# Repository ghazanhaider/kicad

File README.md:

# KiCad

## KiCad bindings

Connect:
```
from kipy import KiCad
kicad = KiCad()
board = KiCad.get_board()
print(f"Connected to KiCad {kicad.get_version()}")
print(f"Active Layer is {board.get_active_layer()}")
```

PCB Tracks:
```
board = KiCad().get_board()
for t in board.get_tracks():
    if (t.layer == board.get_active_layer()) & (t.width not in [156400,156500,142500,300000,500000,180000]):
        print("Width: " + str(t.width) + "  Layer: " + str(t.layer) + " Net: " + str(t.net))
        board.add_to_selection(t)
```

### Older PCBNEW bindings:

```
import pcbnew
board = pcbnew.GetBoard()
tracks = board.GetTracks()
layer = board.GetLayerID("Mid.Cu")
fp_list = brd.GetFootprints()
tracks=board.GetTracks()

badtracks=[]
for t in board.GetTracks()
    print("Width: " + str(t.GetWidth()) + "Layer: " + str(t.GetLayer()))
```

https://www.atomic14.com/2022/10/24/kicad-python-scripting-cheat-sheet
https://kicad.mmccoo.com/index.php/2017/02/01/modifying-pcbnew-layout-from-python/

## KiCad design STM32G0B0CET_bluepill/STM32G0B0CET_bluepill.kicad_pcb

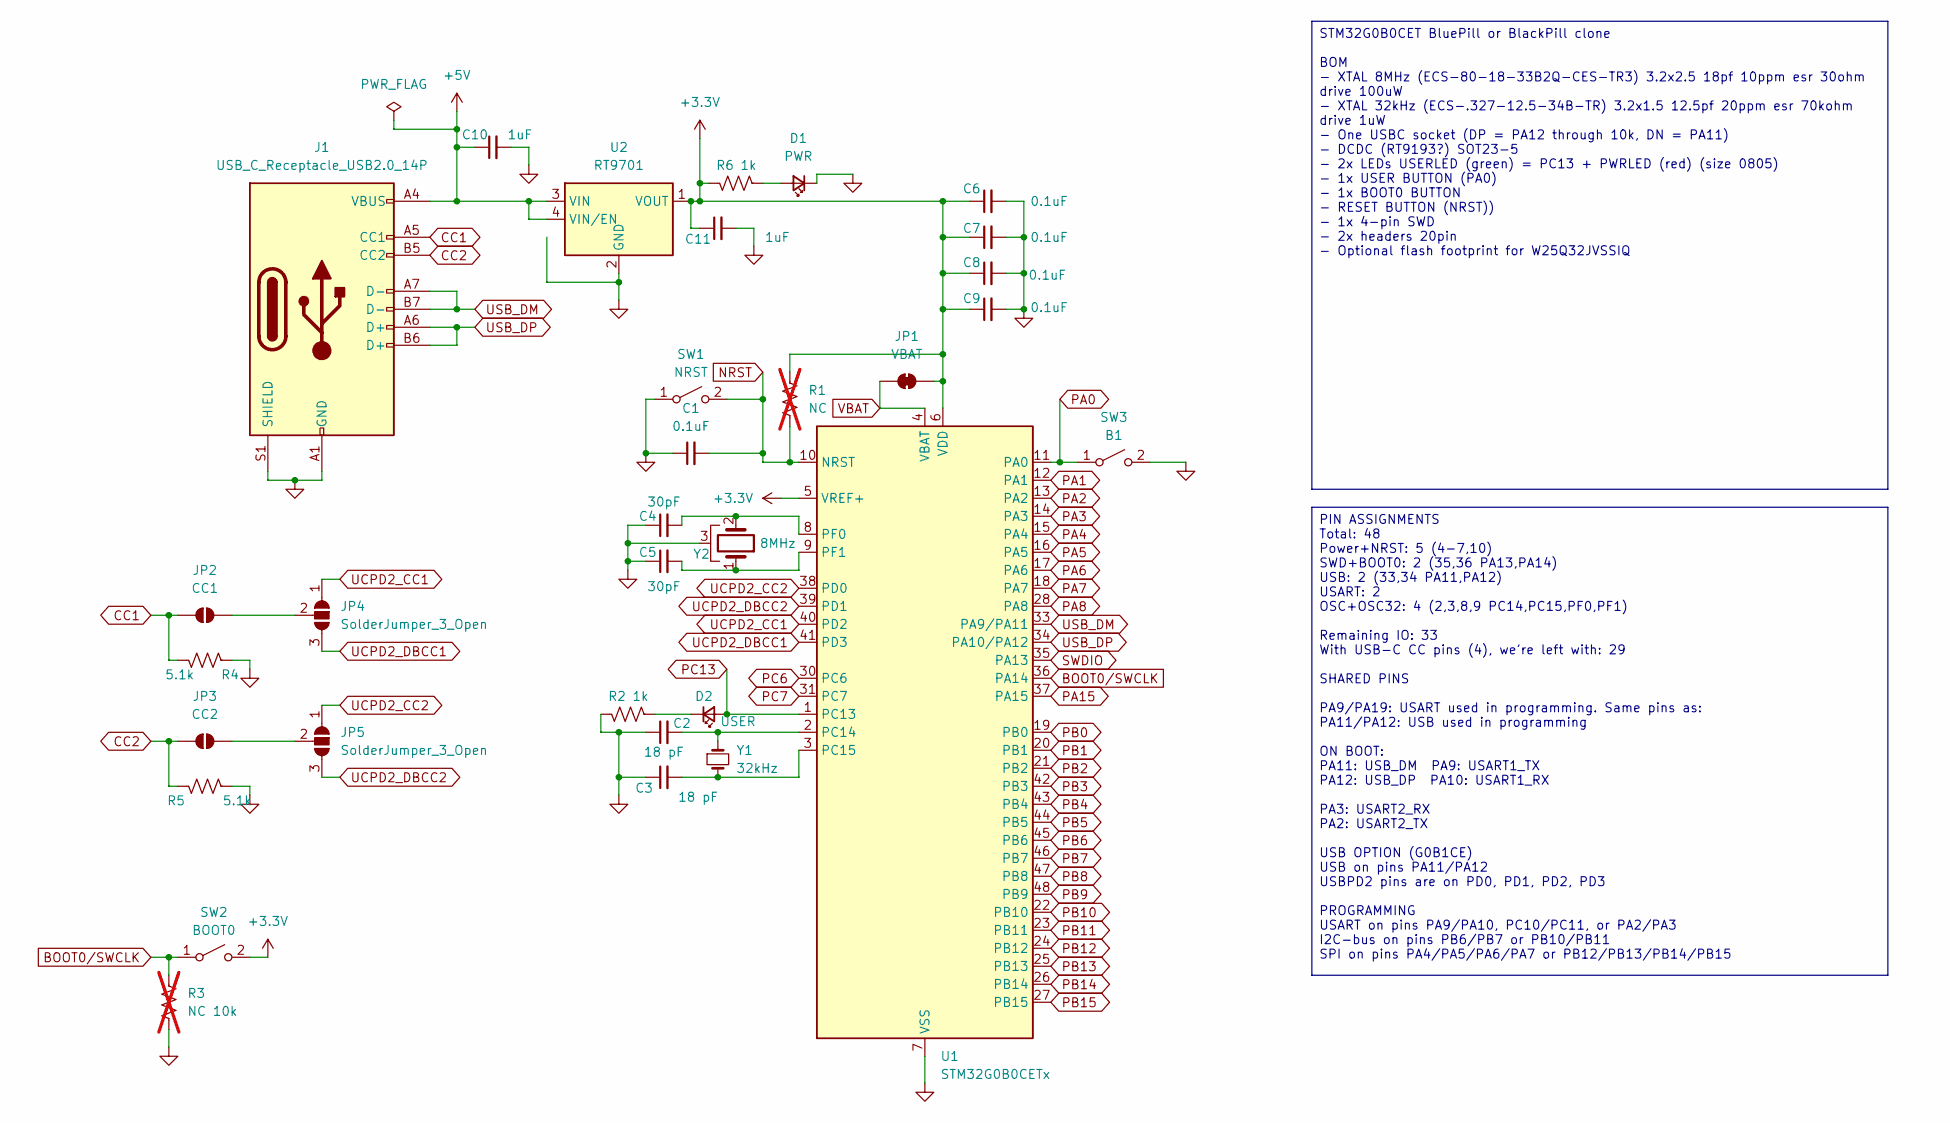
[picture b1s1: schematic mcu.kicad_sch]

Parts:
C1, C6, C7, C8, C9: 0.1uF; C_0603_1608Metric
C2, C3: 18 pF; C_0603_1608Metric
C4, C5: 30pF; C_0603_1608Metric
C10, C11: 1uF; C_0603_1608Metric
D1: PWR; LED_0805_2012Metric
D2: USER; LED_0805_2012Metric
J1: USB_C_Receptacle_USB2.0_14P; USB_C_Receptacle_GCT_USB4105-xx-A_16P_TopMnt_Horizontal
JP1: VBAT; SolderJumper-2_P1.3mm_Bridged_RoundedPad1.0x1.5mm
JP2: CC1; SolderJumper-2_P1.3mm_Open_RoundedPad1.0x1.5mm
JP3: CC2; SolderJumper-2_P1.3mm_Open_RoundedPad1.0x1.5mm
JP4, JP5: SolderJumper_3_Open; SolderJumper-3_P1.3mm_Open_RoundedPad1.0x1.5mm_NumberLabels
R1: NC; R_0603_1608Metric; not fitted
R2, R6: 1k; R_0603_1608Metric
R3: NC 10k; R_0603_1608Metric; not fitted
R4, R5: 5.1k; R_0603_1608Metric
SW1: NRST; SW_SPST_PTS810
SW2: BOOT0; SW_SPST_PTS810
SW3: B1; SW_SPST_PTS810
U1: STM32G0B0CETx; LQFP-48_7x7mm_P0.5mm
U2: RT9701; SOT-23-5
Y1: 32kHz; Crystal_SMD_2012-2Pin_2.0x1.2mm
Y2: 8MHz; Crystal_SMD_3225-4Pin_3.2x2.5mm

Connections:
+3.3V: C6.1, C7.1, C8.1, C9.1, C11.1, JP1.2 (B), R1.1, R6.2, SW2.2 (B), U1.5 (VREF+), U1.6 (VDD), U2.1 (VOUT), U2.5 (VOUT); also elsewhere on the board
+5V: C10.1, J1.A4 (VBUS), J1.A9 (VBUS), J1.B4 (VBUS), J1.B9 (VBUS), U2.3 (VIN), U2.4 (VIN/EN); also elsewhere on the board
BOOT0/SWCLK: R3.1, SW2.1 (A), U1.36 (PA14); also elsewhere on the board
CC1: J1.A5 (CC1), JP2.1 (A), R4.1
CC2: J1.B5 (CC2), JP3.1 (A), R5.2
GND: C1.1, C2.1, C3.1, C4.1, C5.1, C6.2, C7.2, C8.2, C9.2, C10.2, C11.2, D1.1 (K), J1.A1 (GND), J1.A12 (GND), J1.B1 (GND), J1.B12 (GND), J1.S1 (SHIELD), R2.2, R3.2, R4.2, R5.1, SW1.1 (A), SW3.2 (B), U1.7 (VSS), U2.2 (GND), Y2.3; also elsewhere on the board
NRST: C1.2, R1.2, SW1.2 (B), U1.10 (NRST); also elsewhere on the board
unnamed: D1.2 (A), R6.1
unnamed: D2.1 (K), R2.1
unnamed: JP2.2 (B), JP4.2 (C)
unnamed: JP3.2 (B), JP5.2 (C)
unnamed: C2.2, U1.2 (PC14), Y1.1
unnamed: C3.2, U1.3 (PC15), Y1.2
unnamed: C4.2, U1.8 (PF0), Y2.2
unnamed: C5.2, U1.9 (PF1), Y2.1
PA0: SW3.1 (A), U1.11 (PA0); also elsewhere on the board
PA1: U1.12 (PA1); also elsewhere on the board
PA2: U1.13 (PA2); also elsewhere on the board
PA3: U1.14 (PA3); also elsewhere on the board
PA4: U1.15 (PA4); also elsewhere on the board
PA5: U1.16 (PA5); also elsewhere on the board
PA6: U1.17 (PA6); also elsewhere on the board
PA7: U1.18 (PA7); also elsewhere on the board
PA8: U1.28 (PA8); also elsewhere on the board
PA15: U1.37 (PA15); also elsewhere on the board
PB0: U1.19 (PB0); also elsewhere on the board
PB1: U1.20 (PB1); also elsewhere on the board
PB2: U1.21 (PB2); also elsewhere on the board
PB3: U1.42 (PB3); also elsewhere on the board
PB4: U1.43 (PB4); also elsewhere on the board
PB5: U1.44 (PB5); also elsewhere on the board
PB6: U1.45 (PB6); also elsewhere on the board
PB7: U1.46 (PB7); also elsewhere on the board
PB8: U1.47 (PB8); also elsewhere on the board
PB9: U1.48 (PB9); also elsewhere on the board
PB10: U1.22 (PB10); also elsewhere on the board
PB11: U1.23 (PB11); also elsewhere on the board
PB12: U1.24 (PB12); also elsewhere on the board
PB13: U1.25 (PB13); also elsewhere on the board
PB14: U1.26 (PB14); also elsewhere on the board
PB15: U1.27 (PB15); also elsewhere on the board
PC6: U1.30 (PC6); also elsewhere on the board
PC7: U1.31 (PC7); also elsewhere on the board
PC13: D2.2 (A), U1.1 (PC13); also elsewhere on the board
SWDIO: U1.35 (PA13); also elsewhere on the board
UCPD2_CC1: JP4.1 (A), U1.40 (PD2); also elsewhere on the board
UCPD2_CC2: JP5.1 (A), U1.38 (PD0); also elsewhere on the board
UCPD2_DBCC1: JP4.3 (B), U1.41 (PD3)
UCPD2_DBCC2: JP5.3 (B), U1.39 (PD1); also elsewhere on the board
USB_DM: J1.A7 (D-), J1.B7 (D-), U1.33 (PA9/PA11)
USB_DP: J1.A6 (D+), J1.B6 (D+), U1.34 (PA10/PA12)
VBAT: JP1.1 (A), U1.4 (VBAT); also elsewhere on the board

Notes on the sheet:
STM32G0B0CET BluePill or BlackPill clone BOM - XTAL 8MHz (ECS-80-18-33B2Q-CES-TR3) 3.2x2.5 18pf 10ppm esr 30ohm drive 100uW - XTAL 32kHz (ECS-.327-12.5-34B-TR) 3.2x1.5 12.5pf 20ppm esr 70kohm drive 1uW - One USBC socket (DP = PA12 through 10k, DN = PA11) - DCDC (RT9193?) SOT23-5 - 2x LEDs USERLED (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
PIN ASSIGNMENTS Total: 48 Power+NRST: 5 (4-7,10) SWD+BOOT0: 2 (35,36 PA13,PA14) USB: 2 (33,34 PA11,PA12) USART: 2 OSC+OSC32: 4 (2,3,8,9 PC14,PC15,PF0,PF1) Remaining IO: 33 With USB-C CC pins (4), we're left with: 29 SHARED PINS PA9/PA19: USART used in programming. Same pins as: PA11/PA12: USB used 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

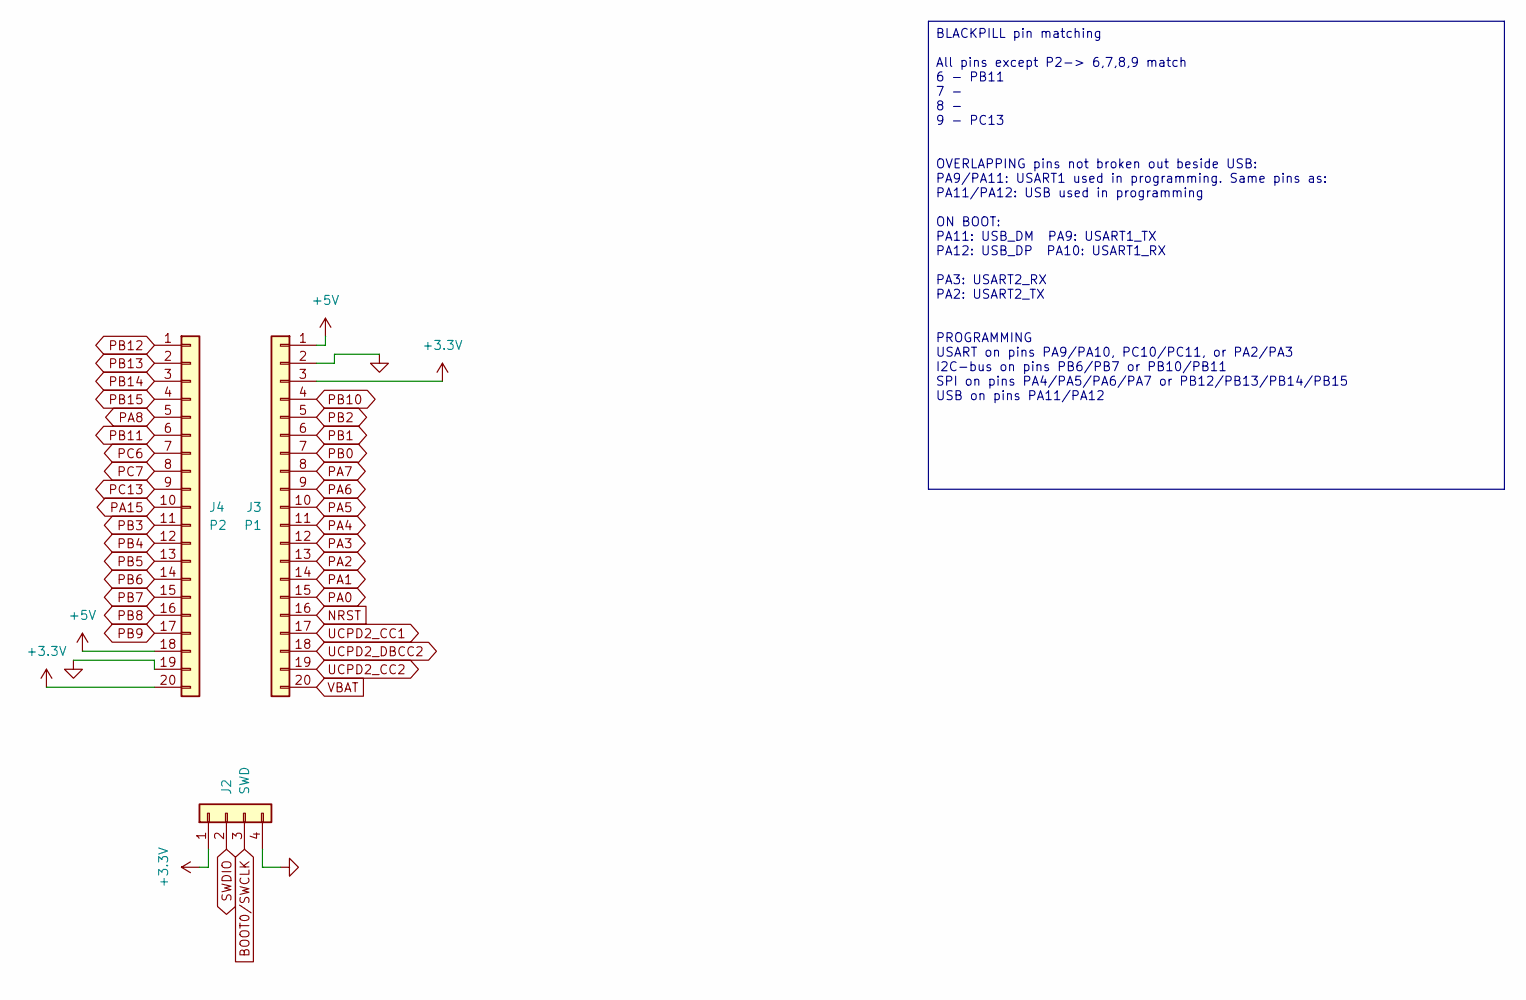
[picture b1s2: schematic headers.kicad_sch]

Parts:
J2: SWD; PinHeader_1x04_P2.54mm_Vertical
J3: P1; PinHeader_1x20_P2.54mm_Vertical
J4: P2; PinHeader_1x20_P2.54mm_Vertical

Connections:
+3.3V: J2.1, J3.3, J4.20; also elsewhere on the board
+5V: J3.1, J4.18; also elsewhere on the board
BOOT0/SWCLK: J2.3; also elsewhere on the board
GND: J2.4, J3.2, J4.19; also elsewhere on the board
NRST: J3.16; also elsewhere on the board
PA0: J3.15; also elsewhere on the board
PA1: J3.14; also elsewhere on the board
PA2: J3.13; also elsewhere on the board
PA3: J3.12; also elsewhere on the board
PA4: J3.11; also elsewhere on the board
PA5: J3.10; also elsewhere on the board
PA6: J3.9; also elsewhere on the board
PA7: J3.8; also elsewhere on the board
PA8: J4.5; also elsewhere on the board
PA15: J4.10; also elsewhere on the board
PB0: J3.7; also elsewhere on the board
PB1: J3.6; also elsewhere on the board
PB2: J3.5; also elsewhere on the board
PB3: J4.11; also elsewhere on the board
PB4: J4.12; also elsewhere on the board
PB5: J4.13; also elsewhere on the board
PB6: J4.14; also elsewhere on the board
PB7: J4.15; also elsewhere on the board
PB8: J4.16; also elsewhere on the board
PB9: J4.17; also elsewhere on the board
PB10: J3.4; also elsewhere on the board
PB11: J4.6; also elsewhere on the board
PB12: J4.1; also elsewhere on the board
PB13: J4.2; also elsewhere on the board
PB14: J4.3; also elsewhere on the board
PB15: J4.4; also elsewhere on the board
PC6: J4.7; also elsewhere on the board
PC7: J4.8; also elsewhere on the board
PC13: J4.9; also elsewhere on the board
SWDIO: J2.2; also elsewhere on the board
UCPD2_CC1: J3.17; also elsewhere on the board
UCPD2_CC2: J3.19; also elsewhere on the board
UCPD2_DBCC2: J3.18; also elsewhere on the board
VBAT: J3.20; also elsewhere on the board

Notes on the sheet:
BLACKPILL pin matching All pins except P2-> 6,7,8,9 match 6 - PB11 7 - 8 - 9 - PC13 OVERLAPPING pins not broken out beside USB: PA9/PA11: USART1 used in programming. Same pins as: PA11/PA12: USB used in programming ON BOOT: PA11: USB_DM PA9: USART1_TX PA12: USB_DP PA10: USART1_RX PA3: USART2_RX PA2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

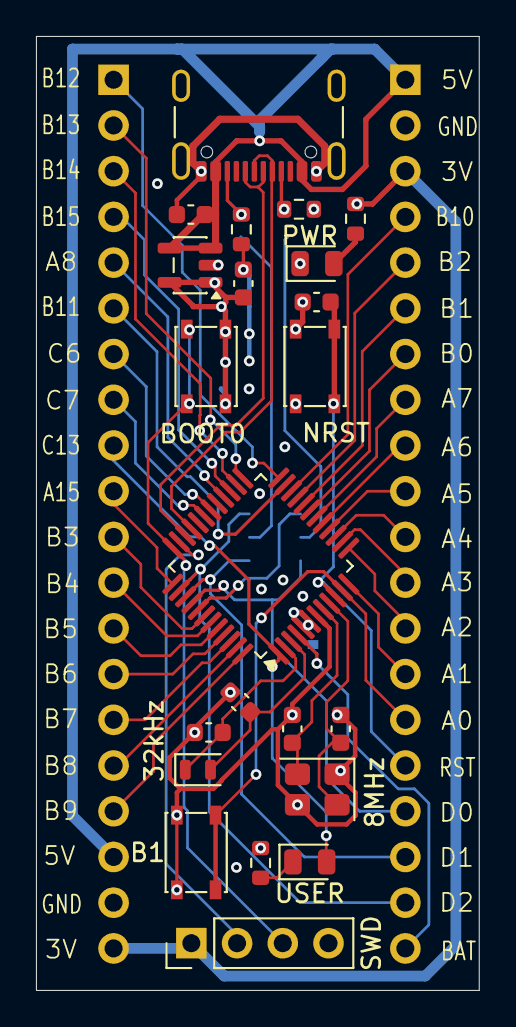
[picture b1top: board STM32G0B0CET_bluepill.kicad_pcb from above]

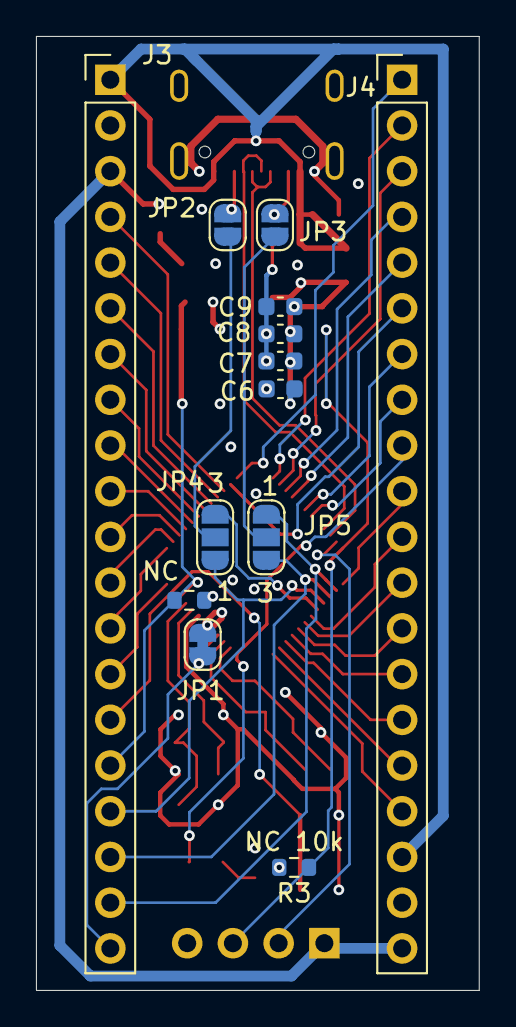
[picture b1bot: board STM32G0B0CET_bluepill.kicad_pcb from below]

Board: 4 copper layers, 24.6 x 53.0 mm, 35 parts (13 on the bottom side), 52 nets.

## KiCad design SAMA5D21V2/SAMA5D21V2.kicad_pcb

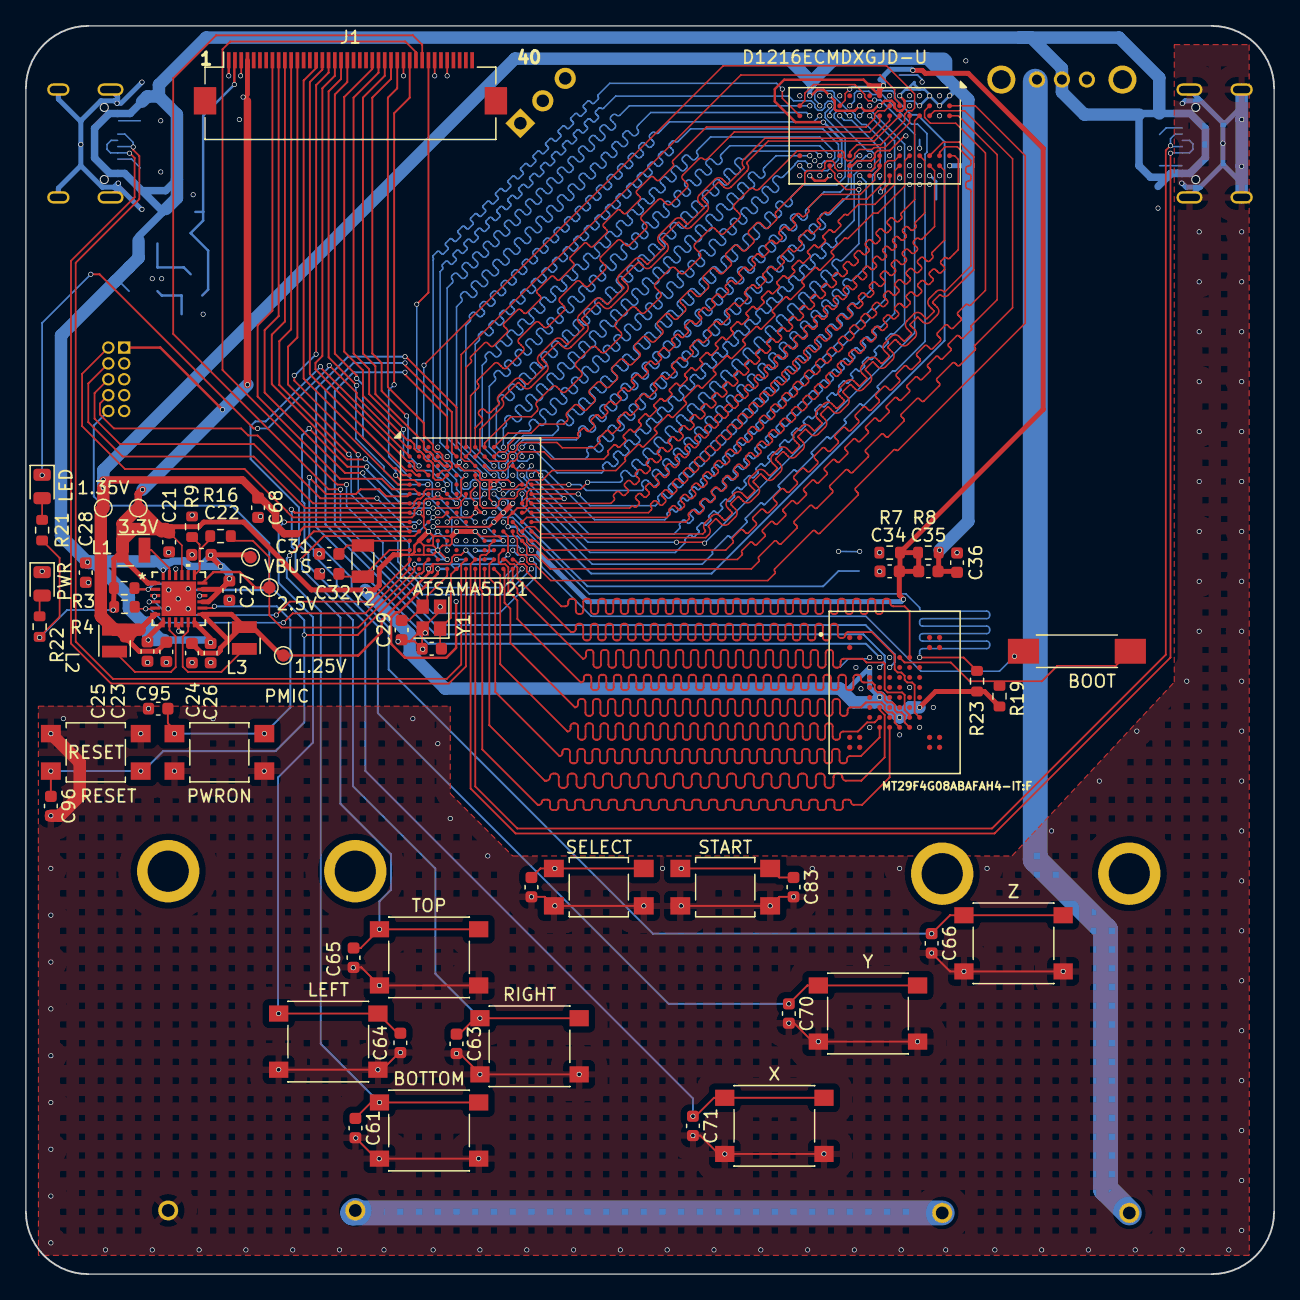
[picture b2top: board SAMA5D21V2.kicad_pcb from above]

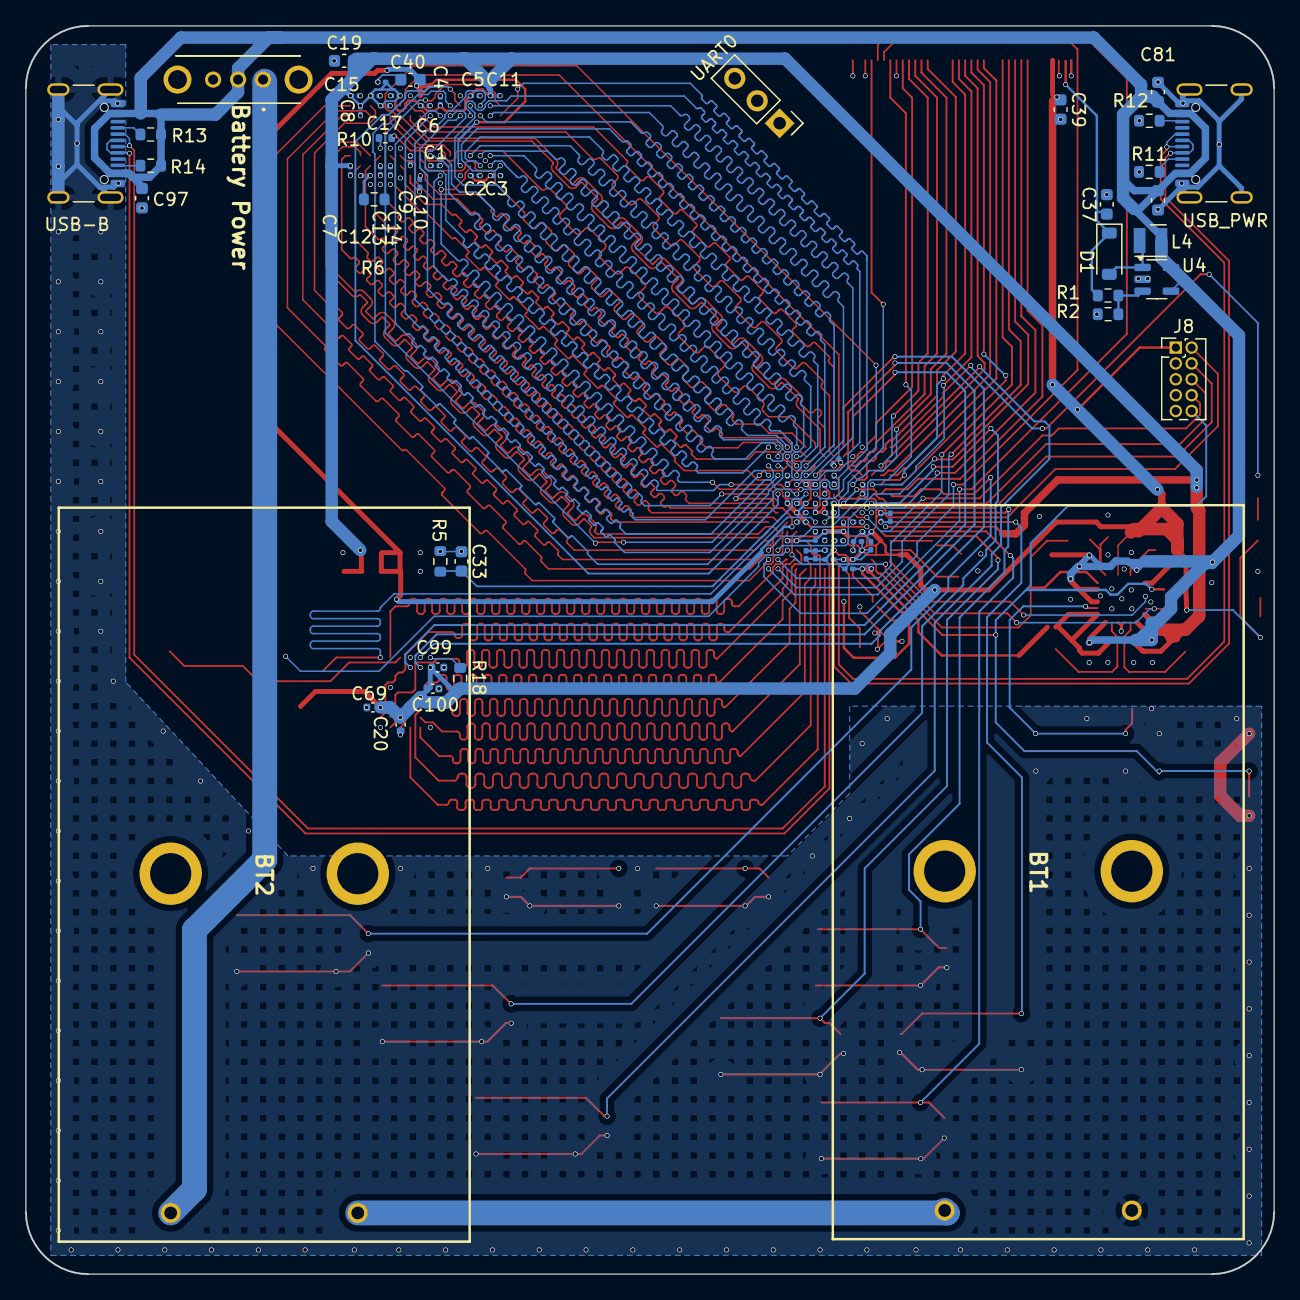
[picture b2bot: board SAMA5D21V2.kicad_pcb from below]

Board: 6 copper layers, 100.0 x 100.0 mm, 149 parts (83 on the bottom side), 136 nets.

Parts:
BT1, BT2: 2.4V; 2462
C1, C2, C3, C4, C5, C6, C7, C8, C9, C10, C11, C12, C13, C14, C15, C16, C17, C18, C38, C41, C42, C43, C44, C45, C46, C47, C48, C49, C50, C51, C52, C53, C54, C55, C57, C58, C67, C72, C74, C76, C78, C79: 100nF; C_0201_0603Metric
C19, C37, C68: 1uF; C_0603_1608Metric
C20, C69, C99, C100: 100nF; C_0402_1005Metric
C21, C23, C24: 22uF; C_0603_1608Metric
C22, C25, C26, C27, C28, C36, C39, C80, C81, C97: 4.7uF; C_0603_1608Metric
C29, C30, C31, C32: 16pF; C_0603_1608Metric
C33: 22pF; C_0603_1608Metric
C34, C35, C40, C61, C63, C64, C65, C66, C70, C71, C82, C83, C95, C96: 100nF; C_0603_1608Metric
C56, C59, C62, C73, C75, C77, C84: 1uF; C_0201_0603Metric
C60: 10nF; C_0201_0603Metric
D1: 1N5819HW-7-F; D_SOD-123
D2: LED; LED_0805_2012Metric
D3: PWR; LED_0805_2012Metric
IC1: D1216ECMDXGJD-U; Micron_FBGA-96_7.5x13.5mm_Layout9x16_P0.8mm
J1: Conn_01x40; Hirose_FH12-40S-0.5SH_1x40-1MP_P0.50mm_Horizontal
J8: SWD; PinHeader_2x05_P1.27mm_Vertical
J10: UART0; PinHeader_1x03_P2.54mm_Vertical
JP1: BOOT; SW_SPST_REED_CT05-XXXX-G1
L1, L2, L3: 2.2uH; L_Wurth_WE-LQSH-2512
L4: 10uH; L_Wurth_WE-LQSH-2512
P1: USB_PWR; USB_C_Receptacle_GCT_USB4105-xx-A_16P_TopMnt_Horizontal
P2: USB-B; USB_C_Receptacle_GCT_USB4105-xx-A_16P_TopMnt_Horizontal
R1: 92.82k; R_0603_1608Metric
R2: 5.1k; R_0603_1608Metric
R3, R4, R6: 100k; R_0603_1608Metric
R5: 23.2k 1%; R_0603_1608Metric
R7, R8: 6.8k 1%; R_0603_1608Metric
R9: 182k; R_0603_1608Metric
R10: 240R 1%; R_0402_1005Metric
R11, R12: 5.1k 1%; R_0603_1608Metric
R13, R14: 56k 1%; R_0603_1608Metric
R15: 5.62k 1%; R_0201_0603Metric
R16: 324k; R_0603_1608Metric
R18, R19: 470k; R_0603_1608Metric
R21, R22, R23: 1k; R_0603_1608Metric
SW1: BOTTOM; SW_Push_1P1T_NO_6x6mm_H9.5mm
SW2: PWRON; SW_SPST_TL3305A
SW3: RESET; SW_SPST_TL3305A
SW4: RIGHT; SW_Push_1P1T_NO_6x6mm_H9.5mm
SW5: LEFT; SW_Push_1P1T_NO_6x6mm_H9.5mm
SW6: TOP; SW_Push_1P1T_NO_6x6mm_H9.5mm
SW7: Z; SW_Push_1P1T_NO_6x6mm_H9.5mm
SW8: Y; SW_Push_1P1T_NO_6x6mm_H9.5mm
SW9: X; SW_Push_1P1T_NO_6x6mm_H9.5mm
SW10: Battery Power; EG1213
SW11: SELECT; SW_SPST_TL3305A
SW12: START; SW_SPST_TL3305A
TP1: VBUS; TestPoint_Pad_D1.0mm
TP2: 3.3V; TestPoint_Pad_D1.0mm
TP3: 1.35V; TestPoint_Pad_D1.0mm
TP4: 1.25V; TestPoint_Pad_D1.0mm
TP5: 2.5V; TestPoint_Pad_D1.0mm
U1: ATSAMA5D21; Microchip_TFBGA-196_11x11mm_Layout14x14_P0.75mm_SMD
U2: PMIC; VQFN24_RMB_MCH
U3: MT29F4G08ABAFAH4-IT:F; BGA63C80P10X12_1050X1300X100N
U4: AP3012; SOT-23-5
Y1: 12MHz; Crystal_SMD_2520-4Pin_2.5x2.0mm
Y2: 32.768kHz; Crystal_SMD_3215-2Pin_3.2x1.5mm

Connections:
+1V25: C24.2, C38.2, C48.1, C49.1, C50.1, C51.1, C52.1, C62.2, C72.1, C73.1, C84.1, L3.1, TP4.1, U1.E8 (VDDCORE), U1.G8 (VDDCORE), U1.H8 (VDDCORE), U1.H9 (VDDCORE), U1.J5 (VDDCORE), U1.M7 (VDDUTMIC), U1.P3 (VDDPLLA), U2.13 (OUT3)
+1V35: C1.2, C2.2, C3.2, C4.2, C5.2, C6.2, C7.2, C8.2, C9.2, C10.2, C11.2, C12.2, C13.2, C14.2, C15.2, C16.2, C17.2, C18.2, C19.2, C23.1, C35.2, C36.1, C41.1, C42.1, C43.1, C44.1, C45.1, C46.1, C47.1, C60.1, C68.1, IC1.A1 (VDDQ_1), IC1.A8 (VDDQ_2), IC1.B2 (VDD_1), IC1.C1 (VDDQ_3), IC1.C9 (VDDQ_4), IC1.D2 (VDDQ_5), IC1.D9 (VDD_2), IC1.E9 (VDDQ_6), IC1.F1 (VDDQ_7), IC1.G7 (VDD_3), IC1.H2 (VDDQ_8), IC1.H9 (VDDQ_9), IC1.K2 (VDD_4), IC1.K8 (VDD_5), IC1.N1 (VDD_6), IC1.N9 (VDD_7), IC1.R1 (VDD_8), IC1.R9 (VDD_9), L2.1, R6.2, R8.1, TP3.1, U1.C6 (VDDIODDR), U1.E10 (VDDIODDR), U1.E12 (VDDIODDR), U1.G10 (VDDIODDR), U1.G12 (VDDIODDR), U1.H11 (VDDIODDR), U1.J10 (VDDIODDR), U2.6 (OUT2)
+3V3: C20.2, C21.1, C39.1, C54.1, C55.1, C56.1, C57.1, C58.1, C59.1, C67.2, C69.2, C74.1, C75.1, C76.1, C77.1, C78.1, C79.1, C99.2, C100.2, J1.4, J8.1 (VTref), L1.2, R3.2, R4.2, R18.1, R19.2, R21.1, R22.1, R23.2, TP2.1, U1.D7 (VDDIOP0), U1.F4 (VDDIOP0), U1.H2 (VDDANA), U1.K3 (VDDANA), U1.K6 (VDDAUDIOPLL), U1.K7 (VDDUTMII), U1.K8 (VDDIOP1), U1.L2 (ADVREF), U1.L11 (VDDIOP1), U1.M4 (VDDBU), U1.N5 (VDDOSC), U2.1 (OUT1), U2.21 (LEN), U3.D3 (VCC), U3.G4 (VCC), U3.H8 (VCC), U3.J6 (VCC)
/DDR3/A0: IC1.N3 (A0), U1.E11 (DDR_A0)
/DDR3/A1: IC1.P7 (A1), U1.C11 (DDR_A1)
/DDR3/A2: IC1.P3 (A2), U1.B12 (DDR_A2)
/DDR3/A3: IC1.N2 (A3), U1.A12 (DDR_A3)
/DDR3/A4: IC1.P8 (A4), U1.D11 (DDR_A4)
/DDR3/A5: IC1.P2 (A5), U1.D14 (DDR_A5)
/DDR3/A6: IC1.R8 (A6), U1.B14 (DDR_A6)
/DDR3/A7: IC1.R2 (A7), U1.D9 (DDR_A7)
/DDR3/A8: IC1.T8 (A8), U1.C10 (DDR_A8)
/DDR3/A9: IC1.R3 (A9), U1.D10 (DDR_A9)
/DDR3/A10/AP: IC1.L7 (A10/AP), U1.F9 (DDR_A10)
/DDR3/A11: IC1.R7 (A11), U1.A11 (DDR_A11)
/DDR3/A12/BC#: IC1.N7 (A12/BC#), U1.B11 (DDR_A12)
/DDR3/A13: IC1.T3 (A13), U1.E13 (DDR_A13)
/DDR3/BA0: IC1.M2 (BA0), U1.F13 (DDR_BA0)
/DDR3/BA1: IC1.N8 (BA1), U1.G13 (DDR_BA1)
/DDR3/BA2: IC1.M3 (BA2), U1.F14 (DDR_BA2)
/DDR3/CAS#: IC1.K3 (CAS#), U1.C13 (DDR_CAS)
/DDR3/CK: IC1.J7 (CK), U1.A13 (DDR_CLK)
/DDR3/CK#: IC1.K7 (CK#), U1.B13 (DDR_CLKN)
/DDR3/CKE: IC1.K9 (CKE), U1.E14 (DDR_CKE)
/DDR3/CS#: IC1.L2 (CS#), U1.F11 (DDR_CS)
/DDR3/DDR_VREF: C34.2, C35.1, C40.1, IC1.H1 (VREFDQ), IC1.M8 (VREFCA), R7.1, R8.2, U1.C12 (DDR_VREF), U1.H12 (DDR_VREF)
/DDR3/DML: IC1.E7 (DML), U1.D8 (DDR_DQM0)
/DDR3/DMU: IC1.D3 (DMU), U1.G14 (DDR_DQM1)
/DDR3/DQL0: IC1.E3 (DQL0), U1.A9 (DDR_D4)
/DDR3/DQL1: IC1.F7 (DQL1), U1.B9 (DDR_D3)
/DDR3/DQL2: IC1.F2 (DQL2), U1.C8 (DDR_D2)
/DDR3/DQL3: IC1.F8 (DQL3), U1.C9 (DDR_D5)
/DDR3/DQL4: IC1.H3 (DQL4), U1.B7 (DDR_D0)
/DDR3/DQL5: IC1.H8 (DQL5), U1.B10 (DDR_D7)
/DDR3/DQL6: IC1.G2 (DQL6), U1.A7 (DDR_D1)
/DDR3/DQL7: IC1.H7 (DQL7), U1.A10 (DDR_D6)
/DDR3/DQSLN: IC1.G3 (DQSL#), U1.A8 (DDR_DQSN0)
/DDR3/DQSLP: IC1.F3 (DQSL), U1.B8 (DDR_DQS0)
/DDR3/DQSUN: IC1.B7 (DQSU#), U1.K13 (DDR_DQSN1)
/DDR3/DQSUP: IC1.C7 (DQSU), U1.K14 (DDR_DQS1)
/DDR3/DQU0: IC1.D7 (DQU0), U1.H13 (DDR_D8)
/DDR3/DQU1: IC1.C3 (DQU1), U1.L13 (DDR_D12)
/DDR3/DQU2: IC1.C8 (DQU2), U1.H14 (DDR_D9)
/DDR3/DQU3: IC1.C2 (DQU3), U1.L14 (DDR_D13)
/DDR3/DQU4: IC1.A7 (DQU4), U1.J14 (DDR_D11)
/DDR3/DQU5: IC1.A2 (DQU5), U1.K12 (DDR_D15)
/DDR3/DQU6: IC1.B8 (DQU6), U1.J13 (DDR_D10)
/DDR3/DQU7: IC1.A3 (DQU7), U1.J12 (DDR_D14)
/DDR3/RAS#: IC1.J3 (RAS#), U1.C14 (DDR_RAS)
/DDR3/WE#: IC1.L3 (WE#), U1.A14 (DDR_WE)
/DDR3/~DDR_RESET: IC1.T2 (RESET#), R6.1, U1.D13 (~DDR_RESET)
/NAND/NAND_CE: JP1.2 (B), R19.1, U3.C6 (CE#)
/Power/SHDN: U1.N1 (SHDN), U2.3 (PWRHLD)
/Power/START: C95.1, SW2.2, U2.14 (nSTRT)
/Power/WKUP: R4.1, U1.P1 (WKUP), U2.5 (nSTRTO)
/USB/USBAN: P1.A7 (D-), P1.B7 (D-), U1.P7 (HHSDMA)
/USB/USBAP: P1.A6 (D+), P1.B6 (D+), U1.N7 (HHSDPA)
/USB/USBBN: P2.A7 (D-), P2.B7 (D-), U1.P8 (HHSDMB)
/USB/USBBP: P2.A6 (D+), P2.B6 (D+), U1.N8 (HHSDPB)
/USB/VBG: R15.2, U1.L7 (VBG)
BUTTON1: C61.1, SW1.2, U1.K1 (PD21)
BUTTON2: C63.1, SW4.2, U1.K2 (PD23)
BUTTON3: C64.1, SW5.2, U1.J1 (PD20)
BUTTON4: C65.1, SW6.2, U1.H1 (PD11)
BUTTON5: C66.1, SW7.2, U1.F1 (PB28)
BUTTON6: C70.1, SW8.2, U1.G3 (PD18)
BUTTON7: C71.1, SW9.2, U1.B1 (PB11)
BUTTON8: C82.1, SW11.2, U1.H3 (PD13)
BUTTON9: C83.1, SW12.2, U1.H4 (PD19)
GNDADIOPLL: BT1.2 (-), C1.1, C2.1, C3.1, C4.1, C5.1, C6.1, C7.1, C8.1, C9.1, C10.1, C11.1, C12.1, C13.1, C14.1, C15.1, C16.1, C17.1, C18.1, C19.1, C20.1, C21.2, C22.2, C23.2, C24.1, C25.2, C26.1, C27.2, C28.1, C29.1, C30.1, C31.2, C32.2, C33.2, C34.1, C36.2, C37.2, C38.1, C39.2, C40.2, C41.2, C42.2, C43.2, C44.2, C45.2, C46.2, C47.2, C48.2, C49.2, C50.2, C51.2, C52.2, C53.2, C54.2, C55.2, C56.2, C57.2, C58.2, C59.2, C60.2, C61.2, C62.1, C63.2, C64.2, C65.2, C66.2, C67.1, C68.2, C69.1, C70.2, C71.2, C72.2, C73.2, C74.2, C75.2, C76.2, C77.2, C78.2, C79.2, C80.2, C81.2, C82.2, C83.2, C84.2, C95.2, C96.2, C97.2, C99.1, C100.1, D3.1 (K), IC1.A9 (VSS_1), IC1.B1 (VSSQ_1), IC1.B3 (VSS_2), IC1.B9 (VSSQ_2), IC1.D1 (VSSQ_3), IC1.D8 (VSSQ_4), IC1.E1 (VSS_3), IC1.E2 (VSSQ_5), IC1.E8 (VSSQ_6), IC1.F9 (VSSQ_7), IC1.G1 (VSSQ_8), IC1.G8 (VSS_4), IC1.G9 (VSSQ_9), IC1.J2 (VSS_5), IC1.J8 (VSS_6), IC1.K1 (ODT), IC1.M1 (VSS_7), IC1.M9 (VSS_8), IC1.P1 (VSS_9), IC1.P9 (VSS_10), IC1.T1 (VSS_11), IC1.T9 (VSS_12), J1.1, J1.3, J1.29, J1.34, J1.36, J8.3 (GND), J8.5 (GND), J8.9 (GNDDetect), J10.1, P1.A1 (GND), P1.A12 (GND), P1.B1 (GND), P1.B12 (GND), P1.S1 (SHIELD), P2.A1 (GND), P2.A12 (GND), P2.B1 (GND), P2.B12 (GND), P2.S1 (SHIELD), R2.2, R5.1, R7.2, R9.2, R10.2, R11.1, R12.1, R15.1, SW1.1, SW2.1, SW3.1, SW4.1, SW5.1, SW6.1, SW7.1, SW8.1, SW9.1, SW11.1, SW12.1, U1.C7 (GNDIODDR), U1.D12 (GNDIODDR), U1.E4 (GNDIOP0), U1.E7 (GNDIOP0), U1.E9 (GNDIODDR), U1.F8 (GNDCORE), U1.F12 (GNDIODDR), U1.G7 (GNDCORE), U1.G9 (GNDCORE), U1.G11 (GNDIODDR), U1.H7 (GNDCORE), U1.H10 (GNDIODDR), U1.J2 (GNDANA), U1.J4 (GNDCORE), U1.J6 (GNDAUDIOPLL), U1.J11 (GNDIODDR), U1.K4 (GNDANA), U1.K9 (GNDIOP1), U1.L6 (GNDDPLL), U1.L8 (GNDUTMII), U1.L12 (GNDIOP1), U1.M5 (GNDBU), U1.M8 (GNDUTMIC), U1.N6 (GNDOSC), U1.P4 (GNDPLLA), U2.4 (LPM), U2.9 (PGND2), U2.10 (PGND3), U2.16 (SGND), U2.22 (PGND1), U2.25 (GND), U3.C5 (VSS), U3.F7 (VSS), U3.K3 (VSS), U3.K8 (VSS), U4.2 (GND), Y1.2, Y1.4
JTAG_TCK: J8.4 (SWCLK/TCK), U1.G6 (PD14)
JTAG_TDI: J8.8 (TX/TDI), U1.H5 (PD15)
JTAG_TDO: J8.6 (SWO/TDO), U1.G1 (PD16)
JTAG_TMS: J8.2 (SWDIO/TMS), U1.G2 (PD17)
LCDDAT3: J1.24, U1.D5 (PB14)
LCDDAT4: J1.25, U1.E5 (PB15)
LCDDAT5: J1.26, U1.C5 (PB16)
LCDDAT6: J1.27, U1.C2 (PB17)
LCDDAT7: J1.28, U1.D4 (PB18)
LCDDAT10: J1.15, U1.D1 (PB21)
LCDDAT11: J1.16, U1.D2 (PB22)
LCDDAT12: J1.17, U1.E1 (PB23)
LCDDAT13: J1.18, U1.D3 (PB24)
LCDDAT14: J1.19, U1.E3 (PB25)
LCDDAT15: J1.20, U1.E2 (PB26)
LCDDAT19: J1.8, U1.F2 (PB30)
LCDDAT20: J1.9, U1.F7 (PB31)
LCDDAT21: J1.10, U1.M13 (PC0)
LCDDAT22: J1.11, U1.P13 (PC1)
LCDDAT23: J1.12, U1.N13 (PC2)
LCDDISP: J1.31, U1.P14 (PC4)
LCDHSYNC: J1.32, U1.N14 (PC6)
LCDPCK: J1.30, U1.M14 (PC7)
LCDVSYNC: J1.33, U1.J8 (PC5)
NANDALE: U1.A6 (PB0), U3.C4 (ALE)
NANDCLE: U1.A5 (PB1), U3.D5 (CLE)
NANDCS3: JP1.1 (A), U1.M12 (PA31)
NANDOE: U1.B6 (PB2), U3.D4 (RE#)
NANDRDY: R23.1, U1.J9 (PC8), U3.C8 (R/B#)
NANDWE: U1.N12 (PA30), U3.C7 (WE#)
NAND_D0: U1.P9 (PA22), U3.H4 (I/O0)
NAND_D1: U1.P10 (PA23), U3.J4 (I/O1)
NAND_D2: U1.N10 (PA24), U3.K4 (I/O2)
NAND_D3: U1.L10 (PA25), U3.K5 (I/O3)
NAND_D4: U1.P11 (PA26), U3.K6 (I/O4)
NAND_D5: U1.P12 (PA27), U3.J7 (I/O5)
NAND_D6: U1.M11 (PA28), U3.K7 (I/O6)
NAND_D7: U1.N11 (PA29), U3.J8 (I/O7)
NRST: C96.1, J8.10 (~RESET), R3.1, SW3.2, U1.N3 (~RST), U2.2 (nRSTO)
unnamed: BT1.1 (+), BT2.2 (-)
unnamed: BT2.1 (+), SW10.1 (A)
unnamed: D1.2 (A), L4.1, U4.1 (SW)
unnamed: C37.1, D1.1 (K), J1.2, R1.1
unnamed: D2.2 (A), R21.2
unnamed: D3.2 (A), R22.2
unnamed: IC1.L8 (ZQ), R10.1
unnamed: P1.A5 (CC1), R11.2
unnamed: P1.B5 (CC2), R12.2
unnamed: P2.A5 (CC1), R13.2
unnamed: P2.B5 (CC2), R14.2
unnamed: C33.1, R5.2, U1.F10 (DDR_CAL)
unnamed: C32.1, U1.M1 (XIN32), Y2.2
unnamed: C31.1, U1.L1 (XOUT32), Y2.1
unnamed: C29.2, U1.P5 (XIN), Y1.3
unnamed: C30.2, U1.P6 (XOUT), Y1.1
unnamed: R9.1, R16.2, U2.19 (LFB)
unnamed: L1.1, U2.23 (SW1)
unnamed: L2.2, U2.8 (SW2)
unnamed: L3.2, U2.11 (SW3)
unnamed: R18.2, U3.C3 (WP#)
unnamed: R1.2, R2.1, U4.3 (FB)
UART4-RX: J10.3, U1.B5 (PB3)
UART4-TX: J10.2, U1.A4 (PB4)
USER_LED: D2.1 (K), U1.A1 (PB10)
VBUS: C22.1, C25.1, C26.2, C27.1, C28.2, C80.1, C81.1, C97.1, L4.2, P1.A4 (VBUS), P1.A9 (VBUS), P1.B4 (VBUS), P1.B9 (VBUS), P2.A4 (VBUS), P2.A9 (VBUS), P2.B4 (VBUS), P2.B9 (VBUS), R13.1, R14.1, SW10.2 (B), TP1.1, U2.7 (PVIN2), U2.12 (PVIN3), U2.15 (SELV3), U2.17 (VIN), U2.24 (PVIN1), U4.4 (~EN), U4.5 (IN)
VDDFUSE: C53.1, R16.1, TP5.1, U1.K11 (VDDFUSE), U2.18 (LOUT)

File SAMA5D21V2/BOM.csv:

"Reference","Value","Datasheet","Footprint","Qty","DNP"
"BT1,BT2","2.4V","~","GhazanCustom:2462","2",""
"C1,C2,C3,C4,C5,C6,C7,C8,C9,C10,C11,C12,C13,C14,C15,C16,C17,C18,C38,C41,C42,C43,C44,C45,C46,C47,C48,C49,C50,C51,C52,C53,C54,C55,C57,C58,C67,C72,C74,C76,C78,C79","100nF","~","Capacitor_SMD:C_0201_0603Metric","42",""
"C19,C37,C68","1uF","-- mixed values --","Capacitor_SMD:C_0603_1608Metric","3",""
"C20,C69,C99,C100","100nF","~","Capacitor_SMD:C_0402_1005Metric","4",""
"C21,C23,C24","22uF","~C1608X5R1A226M080AC","Capacitor_SMD:C_0603_1608Metric","3",""
"C22,C25,C26,C27,C28,C36,C39,C80,C81,C97","4.7uF","-- mixed values --","Capacitor_SMD:C_0603_1608Metric","10",""
"C29,C30,C31,C32","16pF","","Capacitor_SMD:C_0603_1608Metric","4",""
"C33","22pF","~","Capacitor_SMD:C_0603_1608Metric","1",""
"C34,C35,C40,C61,C63,C64,C65,C66,C70,C71,C82,C83,C95,C96","100nF","~","Capacitor_SMD:C_0603_1608Metric","14",""
"C56,C59,C62,C73,C75,C77,C84","1uF","~","Capacitor_SMD:C_0201_0603Metric","7",""
"C60","10nF","~","Capacitor_SMD:C_0201_0603Metric","1",""
"D1","1N5819HW-7-F","~","Diode_SMD:D_SOD-123","1",""
"D2","LED","~","LED_SMD:LED_0805_2012Metric","1",""
"D3","PWR","~","LED_SMD:LED_0805_2012Metric","1",""
"IC1","D1216ECMDXGJD-U","D1216ECMDXGJD-U BGA96C80P9X16_900X1300X120","Package_BGA:Micron_FBGA-96_7.5x13.5mm_Layout9x16_P0.8mm","1",""
"J1","Conn_01x40","~","Connector_FFC-FPC:Hirose_FH12-40S-0.5SH_1x40-1MP_P0.50mm_Horizontal","1",""
"J8","SWD","http://infocenter.arm.com/help/topic/com.arm.doc.ddi0314h/DD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","Connector_PinHeader_1.27mm:PinHeader_2x05_P1.27mm_Vertical","1",""
"J10","UART0","~","Connector_PinHeader_2.54mm:PinHeader_1x03_P2.54mm_Vertical","1",""
"JP1","BOOT","~","Button_Switch_SMD:SW_SPST_REED_CT05-XXXX-G1","1",""
"L1,L2,L3","2.2uH","DFE252012P-2R2M=P2","Inductor_SMD_Wurth:L_Wurth_WE-LQSH-2512","3",""
"L4","10uH","DFE252012P-2R2M=P2","Inductor_SMD_Wurth:L_Wurth_WE-LQSH-2512","1",""
"P1","USB_PWR","https://www.usb.org/sites/default/files/documents/usb_type-c.zip","Connector_USB:USB_C_Receptacle_GCT_USB4105-xx-A_16P_TopMnt_Horizontal","1",""
"P2","USB-B","https://www.usb.org/sites/default/files/documents/usb_type-c.zip","Connector_USB:USB_C_Receptacle_GCT_USB4105-xx-A_16P_TopMnt_Horizontal","1",""
"R1","92.82k","","Resistor_SMD:R_0603_1608Metric","1",""
"R2","5.1k","","Resistor_SMD:R_0603_1608Metric","1",""
"R3,R4,R6","100k","RC0603FR-10100KL","Resistor_SMD:R_0603_1608Metric","3",""
"R5","23.2k 1%","","Resistor_SMD:R_0603_1608Metric","1",""
"R7,R8","6.8k 1%","","Resistor_SMD:R_0603_1608Metric","2",""
"R9","182k","RC0603FR-10100KL","Resistor_SMD:R_0603_1608Metric","1",""
"R10","240R 1%","","Resistor_SMD:R_0402_1005Metric","1",""
"R11,R12","5.1k 1%","","Resistor_SMD:R_0603_1608Metric","2",""
"R13,R14","56k 1%","","Resistor_SMD:R_0603_1608Metric","2",""
"R15","5.62k 1%","","Resistor_SMD:R_0201_0603Metric","1",""
"R16","324k","RC0603FR-10100KL","Resistor_SMD:R_0603_1608Metric","1",""
"R18,R19","470k","AC0603FR-07182KL","Resistor_SMD:R_0603_1608Metric","2",""
"R21,R22,R23","1k","-- mixed values --","Resistor_SMD:R_0603_1608Metric","3",""
"SW1","BOTTOM","~","Button_Switch_SMD:SW_Push_1P1T_NO_6x6mm_H9.5mm","1",""
"SW2","PWRON","~","Button_Switch_SMD:SW_SPST_TL3305A","1",""
"SW3","RESET","~","Button_Switch_SMD:SW_SPST_TL3305A","1",""
"SW4","RIGHT","~","Button_Switch_SMD:SW_Push_1P1T_NO_6x6mm_H9.5mm","1",""
"SW5","LEFT","~","Button_Switch_SMD:SW_Push_1P1T_NO_6x6mm_H9.5mm","1",""
"SW6","TOP","~","Button_Switch_SMD:SW_Push_1P1T_NO_6x6mm_H9.5mm","1",""
"SW7","Z","~","Button_Switch_SMD:SW_Push_1P1T_NO_6x6mm_H9.5mm","1",""
"SW8","Y","~","Button_Switch_SMD:SW_Push_1P1T_NO_6x6mm_H9.5mm","1",""
"SW9","X","~","Button_Switch_SMD:SW_Push_1P1T_NO_6x6mm_H9.5mm","1",""
"SW10","Battery Power","~","GhazanCustom:EG1213","1",""
"SW11","SELECT","~","Button_Switch_SMD:SW_SPST_TL3305A","1",""
"SW12","START","~","Button_Switch_SMD:SW_SPST_TL3305A","1",""
"TP1","VBUS","~","TestPoint:TestPoint_Pad_D1.0mm","1",""
"TP2","3.3V","~","TestPoint:TestPoint_Pad_D1.0mm","1",""
"TP3","1.35V","~","TestPoint:TestPoint_Pad_D1.0mm","1",""
"TP4","1.25V","~","TestPoint:TestPoint_Pad_D1.0mm","1",""
"TP5","2.5V","~","TestPoint:TestPoint_Pad_D1.0mm","1",""
"U1","ATSAMA5D21","http://ww1.microchip.com/downloads/en/DeviceDoc/SAMA5D2-Seri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","Package_BGA:Microchip_TFBGA-196_11x11mm_Layout14x14_P0.75mm_SMD","1",""
"U2","PMIC","MCP16501TA-E/RMB","GhazanCustom:VQFN24_RMB_MCH","1",""
"U3","MT29F4G08ABAFAH4-IT:F","","GhazanCustom:BGA63C80P10X12_1050X1300X100N","1",""
"U4","AP3012","http://www.ti.com/lit/ds/symlink/tps2041.pdf","Package_TO_SOT_SMD:SOT-23-5","1",""
"Y1","12MHz","ECS-120-10-36B2-CWY-TR","Crystal:Crystal_SMD_2520-4Pin_2.5x2.0mm","1",""
"Y2","32.768kHz","ECS-.327-12.5-34B-TR","Crystal:Crystal_SMD_3215-2Pin_3.2x1.5mm","1",""

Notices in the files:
SAMA5D27/SAMA5D27.kicad_pcb:
License GPL-2.0
